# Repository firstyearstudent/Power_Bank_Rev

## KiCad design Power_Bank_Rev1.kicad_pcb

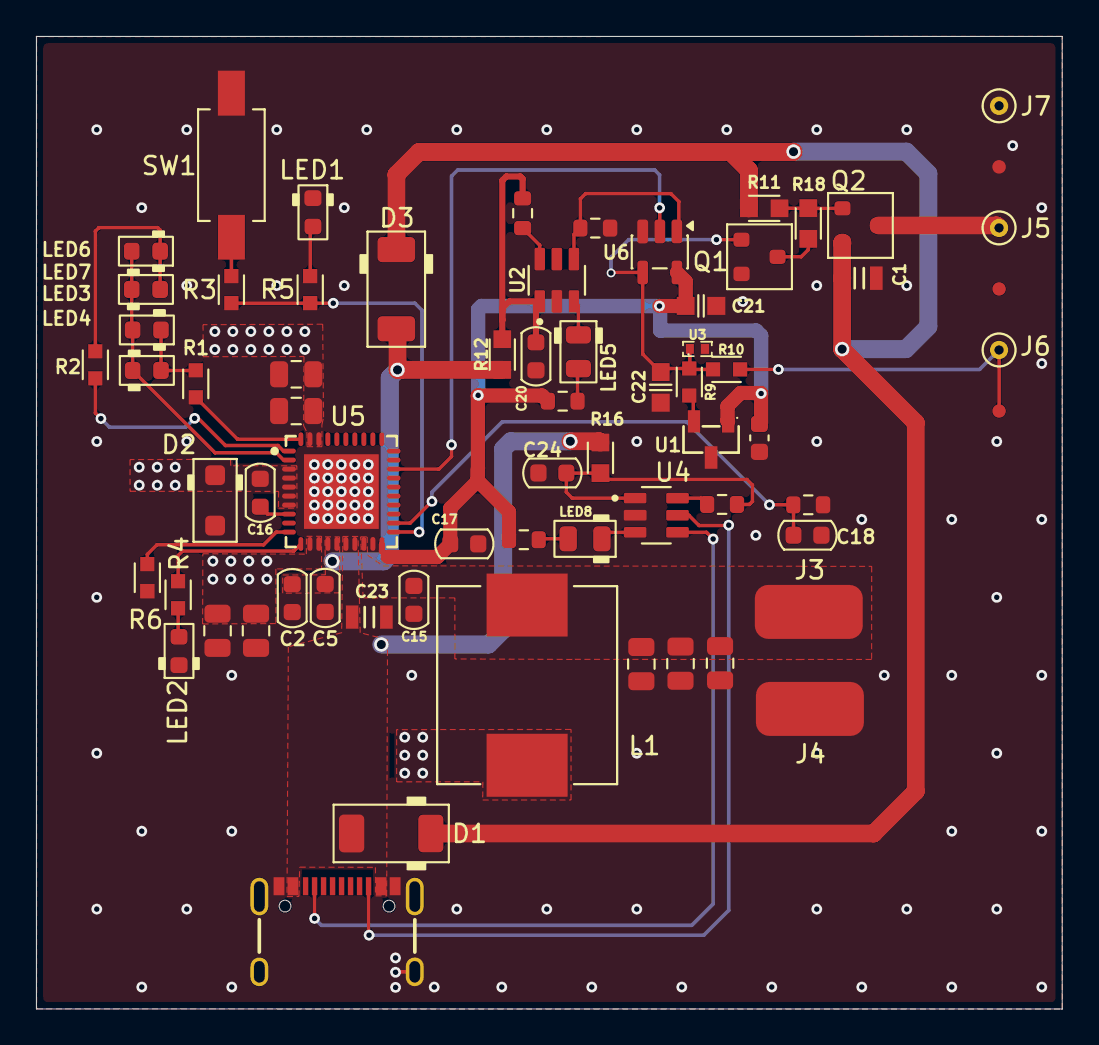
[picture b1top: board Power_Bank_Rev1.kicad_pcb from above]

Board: 2 copper layers, 57.0 x 54.0 mm, 68 parts (0 on the bottom side), 40 nets.

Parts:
C1: 22uF_0805_25V; C_0805
C2, C17: 2.2uF_0603; C_0603_1608Metric
C5, C15, C16, C18: 100nF_0603; C_0603_1608Metric
C8, C9, C10, C11, C12, C13, C14: 22uF; C_0805_2012Metric
C19: 0.1uF; C_0603_1608Metric
C20, C24: 1uF_0603; C_0603_1608Metric
C21: 0.1uF_0603_16V; C_0603
C22: 10nF_0603_25V; C_0603
C23: 10uF_0805_25V; C_0805
D1, D3: PMEG4050EP; D_SOD-128
D2: PMEG4020ER; D_SOD-123F
J1: USB_C_Receptacle; USB-C_16
J3, J4: Conn_01x01; SolderWirePad_1x01_SMD_3x6mm
J5, J6, J7: Pogo_Pin; MILL-MAX_0906-1-15-20-75-14-11-0
L1: 2.2uH; IND_F1F3-1004T-2R2M
LED1, LED2: LED_0603_Red; LED_0603_1608Metric
LED3: 100%; LED_0603_1608Metric
LED4: 75%; LED_0603_1608Metric
LED5, LED8: 100%; LED_0805_2012Metric
LED6: 50%; LED_0603_1608Metric
LED7: 25%; LED_0603_1608Metric
Q1: 2N7002; SOT-23
Q2: AO3407A; SOT-23
R1, R2, R4: 100R_0603; R_0603
R3, R18: 10k_0603; R_0603
R5: 20R_0603; R_0603
R6: 11k_0603; R_0603
R7: 5.1k_DNI; R_0603_1608Metric
R8: 10k; R_0603_1608Metric
R9: 150k_0603; R_0603
R10: 22k_0603; R_0603
R11: 100k_0603; R_0603
R12, R16: 1k_0603; R_0603
R13, R17: 47k; R_0603_1608Metric
R14, R15: 1k; R_0603_1608Metric
SW1: Switch_Tactile_CnK; Button_CnK_PTS636.0_6x3.5mm
TP1, TP2, TP3: 0.75mm; TestPoint-0.75mm
U1: TMAG5231A2DQDBZR; SOT-23-3_L2.9-W1.3-P1.90-LS2.4-BL-1
U2, U4: CH221K; SOT95P280X120-6N
U3: ESD5451N; DFN1006-2L-BI
U5: IP5356; VQFN-40_L6.0-W6.0-P0.50-TL-EP4.2
U6: TS5A3166DBVR; SOT-23-5

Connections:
/12V_RAIL: C1.1, D1.1 (K), D3.1 (K), Q2.2 (S), R11.1
/BAT: C8.1, C9.1, C14.1, C15.1, J3.1 (Pin_1_1), L1.2, U5.18 (BAT)
/CC_BOOST: U5.28 (CC1), U6.2
/CC_IN1: J1.A5 (CC1), U4.4 (CC1)
/CC_IN2: J1.B5 (CC2), U4.5 (CC2)
/IN: C22.1, Q1.1 (G), R9.2, R10.2, U3.1, U6.4
/POGO_12V: J5.1 (1_1), Q2.3 (D), TP1.1 (1_1)
/VBOOST: C2.1, C5.1, D3.2 (A), R12.2, U5.14 (VBUS), U5.15 (VBUS)
/VBUS_IN: C23.1, D1.2 (A), J1.VBUS, R16.2, U5.16 (VIN), U5.17 (VIN)
/VCC: C17.1, C19.2, C21.1, R14.2, R15.2, U1.1 (VCC), U5.20 (VCC), U6.5 (V+)
/VSYS: C10.1, C11.1, C12.1, C13.1, U5.12 (VSYS), U5.13 (VSYS), U5.38 (VSYS), U5.39 (VSYS)
/WATER_DETECT: J6.1 (1_1), R10.1, TP2.1 (1_1)
GND: C1.2, C2.2, C5.2, C8.2, C9.2, C10.2, C11.2, C12.2, C13.2, C14.2, C15.2, C17.2, C18.2, C19.1, C20.2, C21.2, C22.2, C23.2, C24.2, D2.2 (A), J1.GND, J1.S (SHIELD), J4.1 (Pin_1_1), J7.1 (1_1), LED1.1 (K), LED2.1 (K), Q1.2 (S), R6.2, R7.1, R8.2, SW1.2, TP3.1 (1_1), U1.3 (GND), U2.2 (GND), U3.2, U4.2 (GND), U5.19 (AGND), U5.41 (EPAD), U6.3 (GND)
unnamed: C16.2, D2.1 (K), L1.1, U5.3 (LX), U5.4 (LX), U5.5 (LX), U5.6 (LX), U5.7 (LX)
unnamed: J1.A7 (D-), J1.B7 (D-)
unnamed: LED1.2 (A), R5.1
unnamed: LED2.2 (A), R4.2
unnamed: LED3.2 (A), LED4.1 (K), LED6.2 (A), LED7.1 (K), U5.2 (LED3)
unnamed: LED3.1 (K), LED4.2 (A), R1.2
unnamed: LED5.2 (A), R14.1
unnamed: LED5.1 (K), U2.3 (~PG)
unnamed: LED6.1 (K), LED7.2 (A), R2.2
unnamed: LED8.2 (A), R15.1
unnamed: LED8.1 (K), U4.3 (~PG)
unnamed: Q1.3 (D), R18.2
unnamed: Q2.1 (G), R11.2, R18.1
unnamed: R3.2, SW1.1
unnamed: R9.1, U1.2 (OUT)
unnamed: R7.2, U2.4 (CC1), U6.1
unnamed: R13.1, U2.6 (CFG)
unnamed: C20.1, R12.1, R13.2, U2.1 (VDD)
unnamed: R17.1, U4.6 (CFG)
unnamed: C24.1, R16.1, R17.2, U4.1 (VDD)
unnamed: C16.1, U5.8 (BST)
unnamed: R3.1, R5.2, U5.21 (KEY)
unnamed: R1.1, U5.40 (LED1)
unnamed: R2.1, U5.1 (LED2)
unnamed: R6.1, U5.10 (LED5)
unnamed: R4.1, U5.11 (LED6)
unnamed: C18.1, R8.1, U5.22 (NTC)
